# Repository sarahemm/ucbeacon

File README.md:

# ucbeacon
Unicamp Campsite Beacon

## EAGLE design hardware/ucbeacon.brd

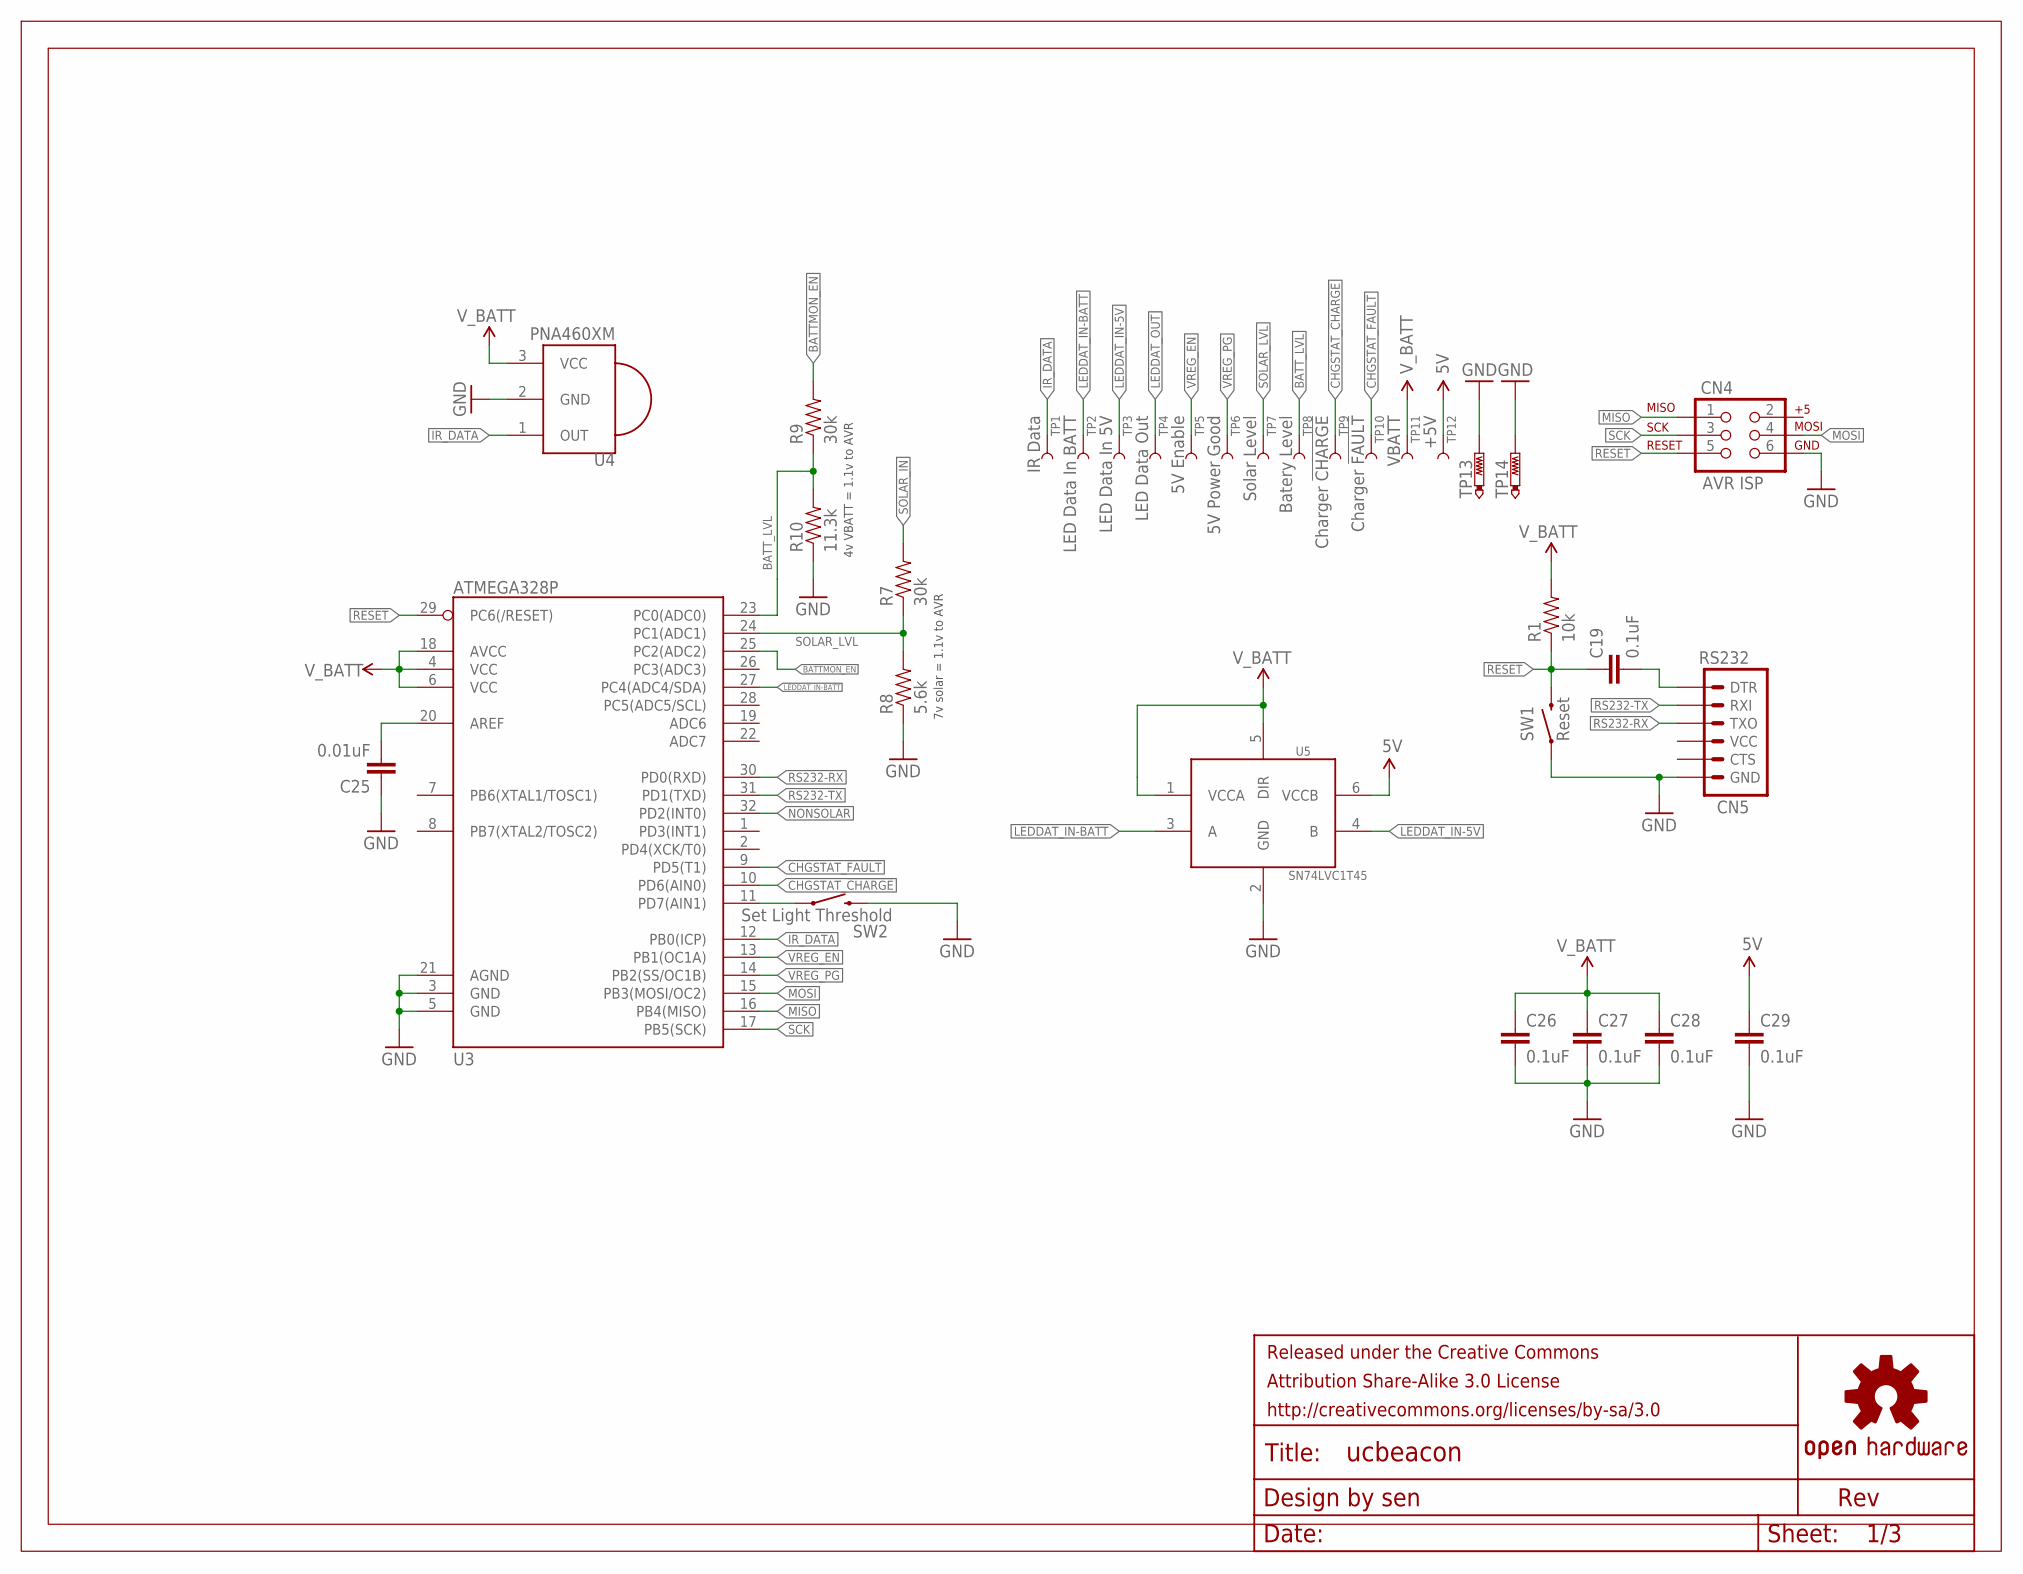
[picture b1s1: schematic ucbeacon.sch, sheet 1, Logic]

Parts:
C19, C26, C27, C28, C29: 0.1uF; 0603-CAP
C25: 0.01uF; 0603-CAP
CN4: AVR ISP; 2X3_LOCK
CN5: RS232; 1X06_LOCK
FRAME2: FRAME-LETTER-GRID-OSHW-SENOSHW-LOGO-L; OSHW-LOGO-L
R1: 10k; 0603-RES
R7, R9: 30k; 0603-RES
R8: 5.6k; 0603-RES
R10: 11.3k; 0603-RES
SW1: Reset; TACTILE_SWITCH_TALL
SW2: Set Light Threshold; TACTILE_SWITCH_TALL
TP1: IR Data; TP_15TH-MASKBOT
TP2: LED Data In BATT; TP_15TH-MASKBOT
TP3: LED Data In 5V; TP_15TH-MASKBOT
TP4: LED Data Out; TP_15TH-MASKBOT
TP5: 5V Enable; TP_15TH-MASKBOT
TP6: 5V Power Good; TP_15TH-MASKBOT
TP7: Solar Level; TP_15TH-MASKBOT
TP8: Batery Level; TP_15TH-MASKBOT
TP9: Charger !CHARGE; TP_15TH-MASKBOT
TP10: Charger !FAULT; TP_15TH-MASKBOT
TP11: VBATT; TP_15TH-MASKBOT
TP12: +5V; TP_15TH
TP13, TP14: GND; P1-13
U3: ATMEGA328P; TQFP32-08
U4: PNA460XM
U5: SN74LVC1T45; SOT23-6L

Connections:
5V: C29.1, TP12.P$1, U5.6 (VCCB); also elsewhere on the board
!RESET: C19.1, CN4.5, R1.1, SW1.B2 (2), U3.29 (PC6(/RESET))
AREF: C25.2, U3.20 (AREF)
BATTMON_EN: R9.2, U3.25 (PC2(ADC2))
BATT_LVL: R9.1, R10.2, TP8.P$1, U3.23 (PC0(ADC0))
CHGSTAT_!CHARGE: TP9.P$1, U3.10 (PD6(AIN0)); also elsewhere on the board
CHGSTAT_!FAULT: TP10.P$1, U3.9 (PD5(T1)); also elsewhere on the board
DTR_RESET: C19.2, CN5.1 (DTR)
GND: C25.1, C26.2, C27.2, C28.2, C29.2, CN4.6, CN5.6 (GND), R8.1, R10.1, SW1.A2 (1), SW2.B2 (2), TP13.TP, TP14.TP, U3.3 (GND), U3.5 (GND), U3.21 (AGND), U4.2 (GND), U5.2 (GND); also elsewhere on the board
IR_DATA: TP1.P$1, U3.12 (PB0(ICP)), U4.1 (OUT)
LEDDAT_IN-5V: TP3.P$1, U5.4 (B); also elsewhere on the board
LEDDAT_IN-BATT: TP2.P$1, U3.27 (PC4(ADC4/SDA)), U5.3 (A); also elsewhere on the board
LEDDAT_OUT: TP4.P$1; also elsewhere on the board
MISO: CN4.1, U3.16 (PB4(MISO))
MOSI: CN4.4, U3.15 (PB3(MOSI/OC2))
NONSOLAR: U3.32 (PD2(INT0)); also elsewhere on the board
RS232-RX: CN5.3 (TXO), U3.30 (PD0(RXD))
RS232-TX: CN5.2 (RXI), U3.31 (PD1(TXD))
SCK: CN4.3, U3.17 (PB5(SCK))
SET_LIGHT_THRESH: SW2.A2 (1), U3.11 (PD7(AIN1))
SOLAR_IN: R7.2; also elsewhere on the board
SOLAR_LVL: R7.1, R8.2, TP7.P$1, U3.24 (PC1(ADC1))
VREG_EN: TP5.P$1, U3.13 (PB1(OC1A)); also elsewhere on the board
VREG_PG: TP6.P$1, U3.14 (PB2(SS/OC1B)); also elsewhere on the board
V_BATT: C26.1, C27.1, C28.1, R1.2, TP11.P$1, U3.4 (VCC), U3.6 (VCC), U3.18 (AVCC), U4.3 (VCC), U5.1 (VCCA), U5.5 (DIR); also elsewhere on the board

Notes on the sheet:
7v solar = 1.1v to AVR
4v VBATT = 1.1v to AVR

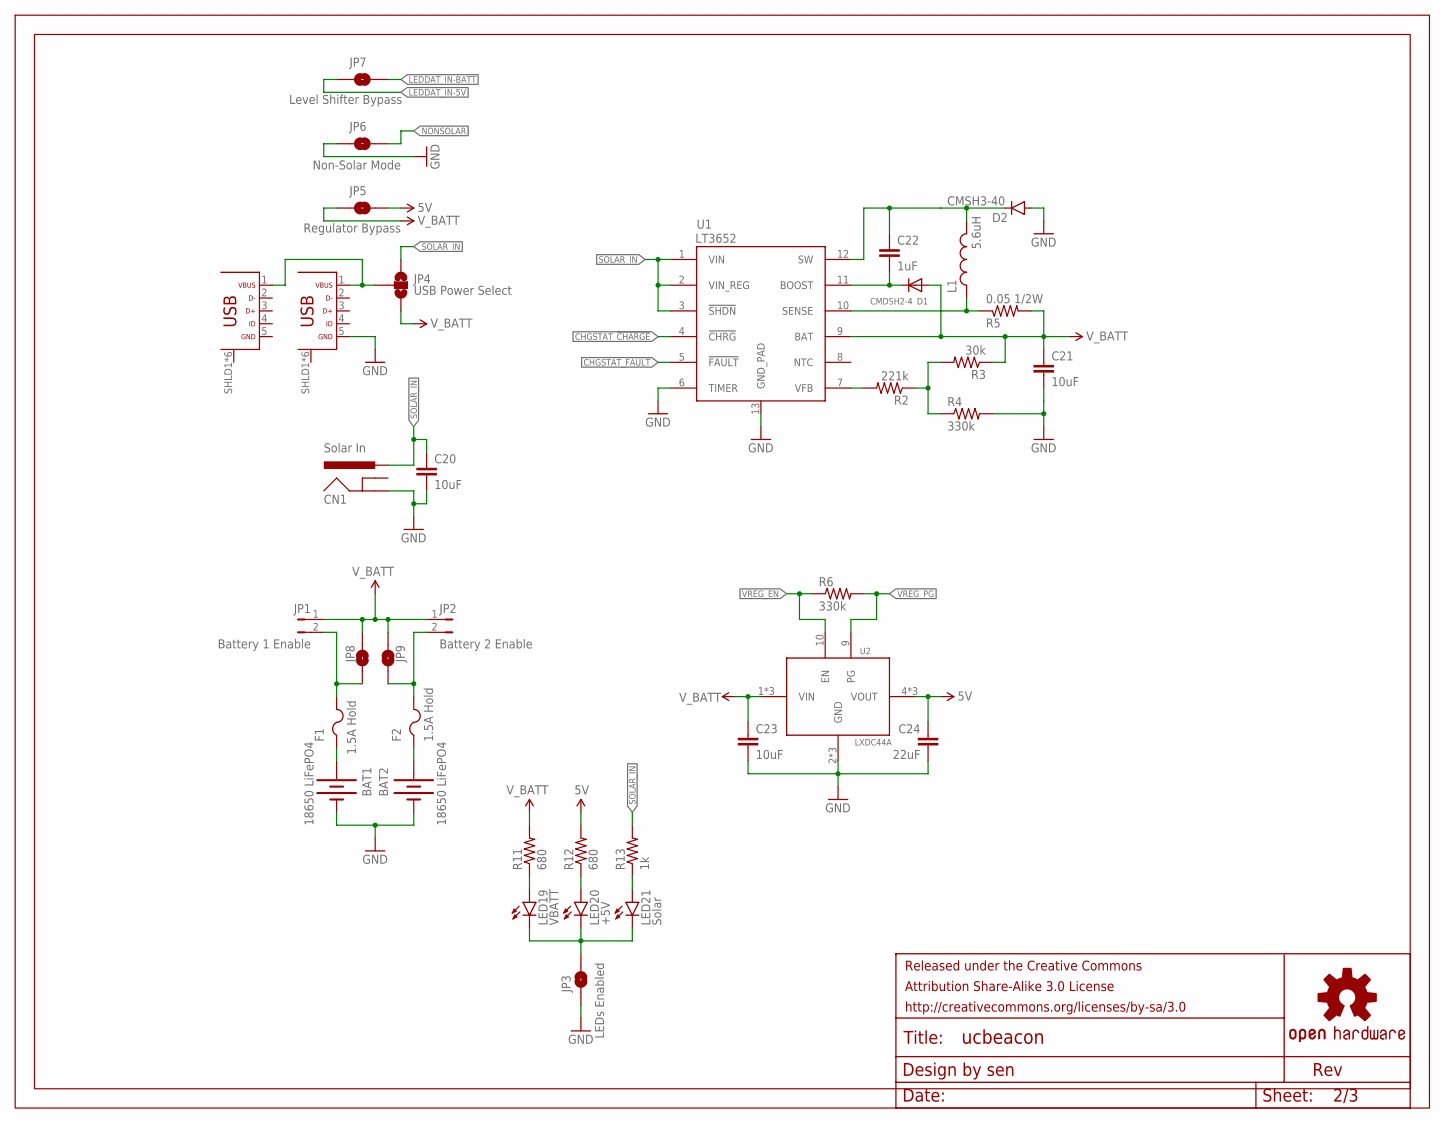
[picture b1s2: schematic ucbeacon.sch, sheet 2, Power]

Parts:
BAT1, BAT2: 18650 LiFePO4; BATTERY_18650-HOLDER
C20, C21, C23: 10uF; 0805-CAP
C22: 1uF; 0402-CAP
C24: 22uF; 0805
CN1: Solar In; POWER_JACK_PTH_LOCK
CN2: Bottom USB; FCI-10118194-MICROUSB
CN3: Top USB; FCI-10118194-MICROUSB
D1: CMDSH2-4; SOD-323F
D2: CMSH3-40; SMA-DIODE
F1, F2: 1.5A Hold; 1812
FRAME3: FRAME-LETTER-GRID-OSHW-SENOSHW-LOGO-L; OSHW-LOGO-L
JP1: Battery 1 Enable; PTH-JUMPER-2-NO_NO_SILK
JP2: Battery 2 Enable; PTH-JUMPER-2-NO_NO_SILK
JP3: LEDs Enabled; PAD-JUMPER-2-NO_YES_SILK
JP4: USB Power Select; PAD-JUMPER-3-NO_YES_SILK
JP5: Regulator Bypass; PAD-JUMPER-2-NO_YES_SILK
JP6: Non-Solar Mode; PAD-JUMPER-2-NO_YES_SILK
JP7: Level Shifter Bypass; PAD-JUMPER-2-NO_YES_SILK
JP8, JP9: Battery 1 Enable; PAD-JUMPER-2-NO_YES_SILK
L1: 5.6uH; PULSE-P1167
LED19: VBATT; LED-1206
LED20: +5V; LED-1206
LED21: Solar; LED-1206
R2: 221k; 0603-RES
R3: 30k; 0603-RES
R4, R6: 330k; 0603-RES
R5: 0.05 1/2W; 1206
R11, R12: 680; 0603-RES
R13: 1k; 0603-RES
U1: LT3652; MSOP-12_GND
U2: LXDC44A

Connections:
5V: C24.1, JP5.2, R12.2, U2.4 (VOUT), U2.5 (VOUT), U2.6 (VOUT); also elsewhere on the board
5V_LED: LED20.A, R12.1
BAT1_F: BAT1.PWR@1 (+), F1.1
BAT1_PREJMP: F1.2, JP1.2, JP8.2
BAT2_F: BAT2.PWR@1 (+), F2.1
BAT2_PREJMP: F2.2, JP2.2, JP9.2
CHGSTAT_!CHARGE: U1.4 (!CHRG); also elsewhere on the board
CHGSTAT_!FAULT: U1.5 (!FAULT); also elsewhere on the board
CHG_BOOST: C22.2, D1.C, U1.11 (BOOST)
CHG_SENSE: L1.2, R5.1, U1.10 (SENSE)
CHG_SW: C22.1, D2.C, L1.1, U1.12 (SW)
CHG_VFB: R2.2, U1.7 (VFB)
CHG_VFB_CTR: R2.1, R3.2, R4.1
GND: BAT1.GND@1 (-), BAT2.GND@1 (-), C20.2, C21.2, C23.2, C24.2, CN1.GND, CN2.5 (GND), CN3.5 (GND), D2.A, JP3.1, JP6.1, R4.2, U1.6 (TIMER), U1.13 (GND_PAD), U2.2 (GND), U2.3 (GND), U2.8 (GND); also elsewhere on the board
LEDDAT_IN-5V: JP7.1; also elsewhere on the board
LEDDAT_IN-BATT: JP7.2; also elsewhere on the board
LED_GND: JP3.2, LED19.C, LED20.C, LED21.C
NONSOLAR: JP6.2; also elsewhere on the board
SOLAR_IN: C20.1, CN1.PWR, JP4.1, R13.2, U1.1 (VIN), U1.2 (VIN_REG), U1.3 (!SHDN); also elsewhere on the board
SOLAR_LED: LED21.A, R13.1
USB_VBUS: CN2.1 (VBUS), CN3.1 (VBUS), JP4.2
VBATT_LED: LED19.A, R11.1
VREG_EN: R6.1, U2.10 (EN); also elsewhere on the board
VREG_PG: R6.2, U2.9 (PG); also elsewhere on the board
V_BATT: C21.1, C23.1, D1.A, JP1.1, JP2.1, JP4.3, JP5.1, JP8.1, JP9.1, R3.1, R5.2, R11.2, U1.9 (BAT), U2.1 (VIN), U2.11 (VIN), U2.12 (VIN); also elsewhere on the board

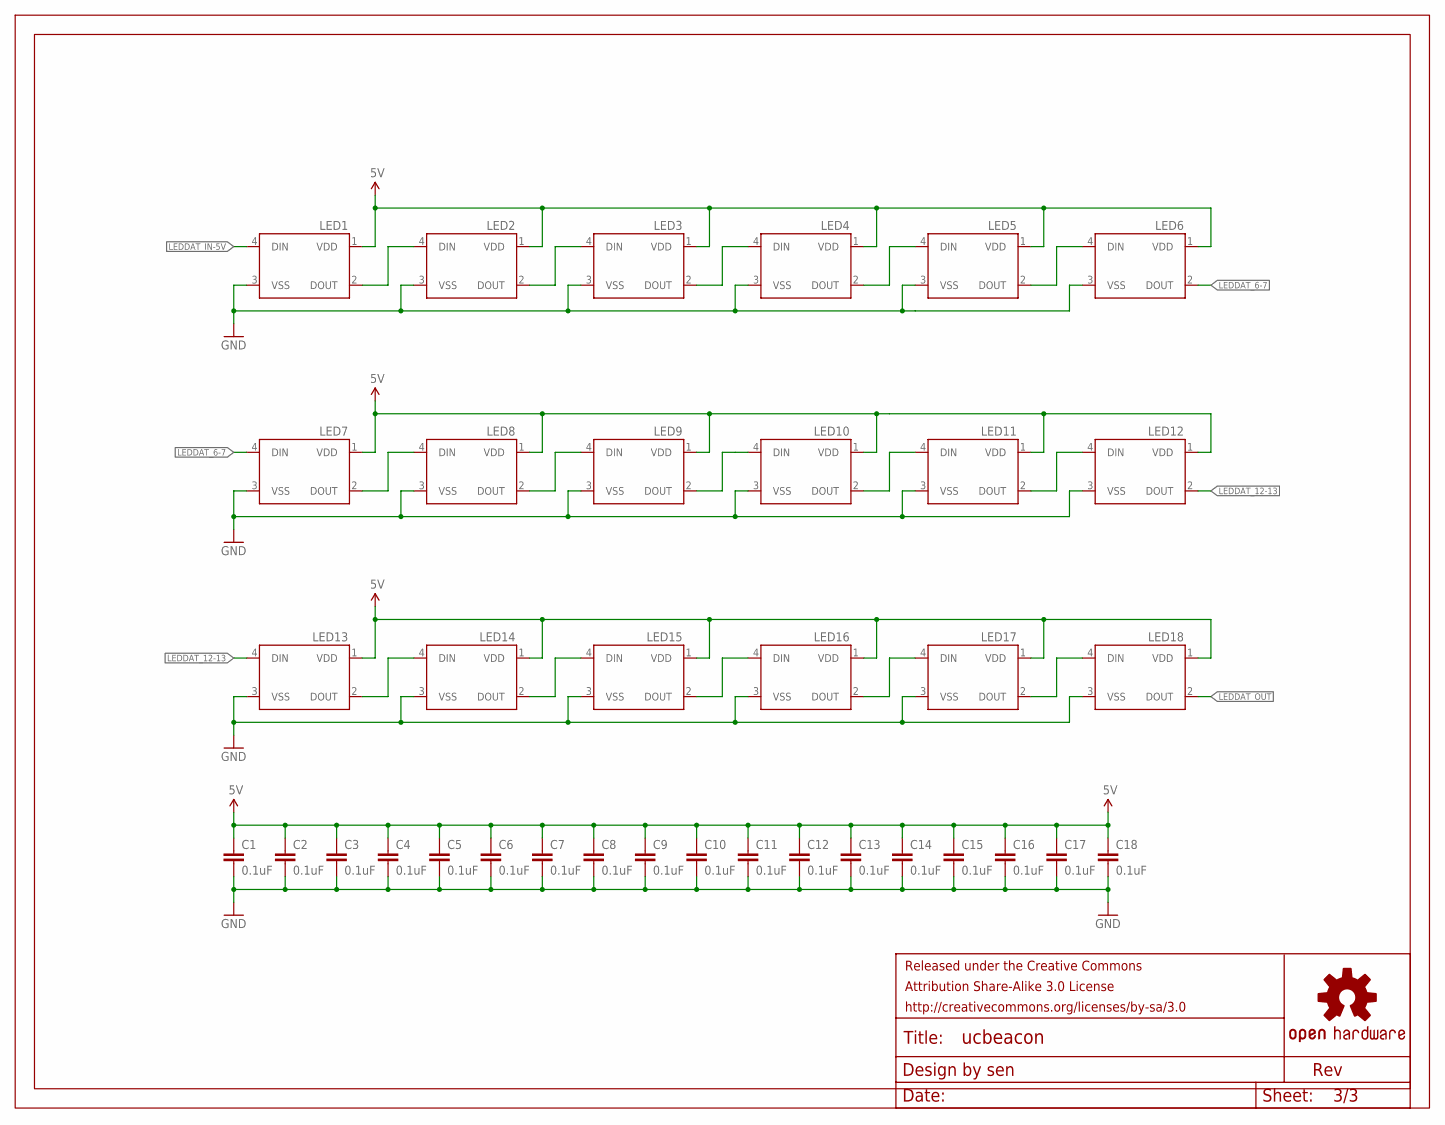
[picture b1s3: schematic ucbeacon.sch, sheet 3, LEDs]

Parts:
C1, C2, C3, C4, C5, C6, C7, C8, C9, C10, C11, C12, C13, C14, C15, C16, C17, C18: 0.1uF; 0603-CAP
FRAME1: FRAME-LETTER-GRID-OSHW-SENOSHW-LOGO-L; OSHW-LOGO-L
LED1, LED2, LED3, LED4, LED5, LED6, LED7, LED8, LED9, LED10, LED11, LED12, LED13, LED14, LED15, LED16, LED17, LED18: WS2812B

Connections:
5V: C1.1, C2.1, C3.1, C4.1, C5.1, C6.1, C7.1, C8.1, C9.1, C10.1, C11.1, C12.1, C13.1, C14.1, C15.1, C16.1, C17.1, C18.1, LED1.1 (VDD), LED2.1 (VDD), LED3.1 (VDD), LED4.1 (VDD), LED5.1 (VDD), LED6.1 (VDD), LED7.1 (VDD), LED8.1 (VDD), LED9.1 (VDD), LED10.1 (VDD), LED11.1 (VDD), LED12.1 (VDD), LED13.1 (VDD), LED14.1 (VDD), LED15.1 (VDD), LED16.1 (VDD), LED17.1 (VDD), LED18.1 (VDD); also elsewhere on the board
GND: C1.2, C2.2, C3.2, C4.2, C5.2, C6.2, C7.2, C8.2, C9.2, C10.2, C11.2, C12.2, C13.2, C14.2, C15.2, C16.2, C17.2, C18.2, LED1.3 (VSS), LED2.3 (VSS), LED3.3 (VSS), LED4.3 (VSS), LED5.3 (VSS), LED6.3 (VSS), LED7.3 (VSS), LED8.3 (VSS), LED9.3 (VSS), LED10.3 (VSS), LED11.3 (VSS), LED12.3 (VSS), LED13.3 (VSS), LED14.3 (VSS), LED15.3 (VSS), LED16.3 (VSS), LED17.3 (VSS), LED18.3 (VSS); also elsewhere on the board
LEDDAT_1-2: LED1.2 (DOUT), LED2.4 (DIN)
LEDDAT_2-3: LED2.2 (DOUT), LED3.4 (DIN)
LEDDAT_3-4: LED3.2 (DOUT), LED4.4 (DIN)
LEDDAT_4-5: LED4.2 (DOUT), LED5.4 (DIN)
LEDDAT_5-6: LED5.2 (DOUT), LED6.4 (DIN)
LEDDAT_6-7: LED6.2 (DOUT), LED7.4 (DIN)
LEDDAT_7-8: LED7.2 (DOUT), LED8.4 (DIN)
LEDDAT_8-9: LED8.2 (DOUT), LED9.4 (DIN)
LEDDAT_9-10: LED9.2 (DOUT), LED10.4 (DIN)
LEDDAT_10-11: LED10.2 (DOUT), LED11.4 (DIN)
LEDDAT_11-12: LED11.2 (DOUT), LED12.4 (DIN)
LEDDAT_12-13: LED12.2 (DOUT), LED13.4 (DIN)
LEDDAT_13-14: LED13.2 (DOUT), LED14.4 (DIN)
LEDDAT_14-15: LED14.2 (DOUT), LED15.4 (DIN)
LEDDAT_15-16: LED15.2 (DOUT), LED16.4 (DIN)
LEDDAT_16-17: LED16.2 (DOUT), LED17.4 (DIN)
LEDDAT_17-18: LED17.2 (DOUT), LED18.4 (DIN)
LEDDAT_IN-5V: LED1.4 (DIN); also elsewhere on the board
LEDDAT_OUT: LED18.2 (DOUT); also elsewhere on the board

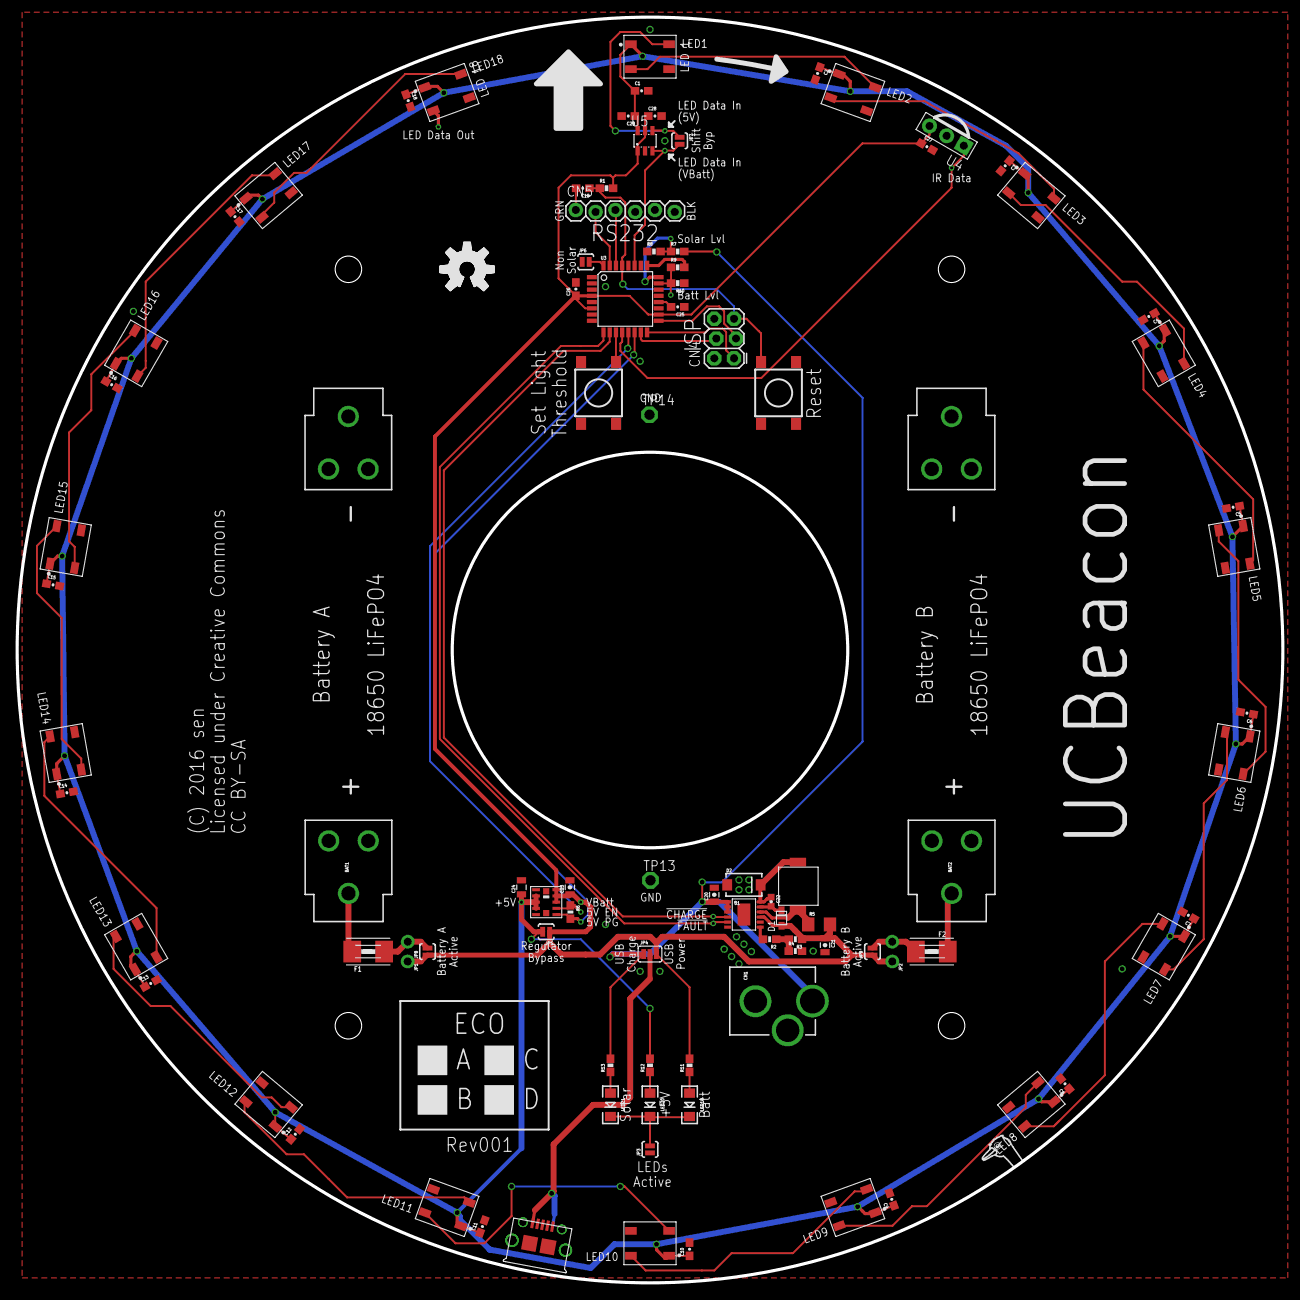
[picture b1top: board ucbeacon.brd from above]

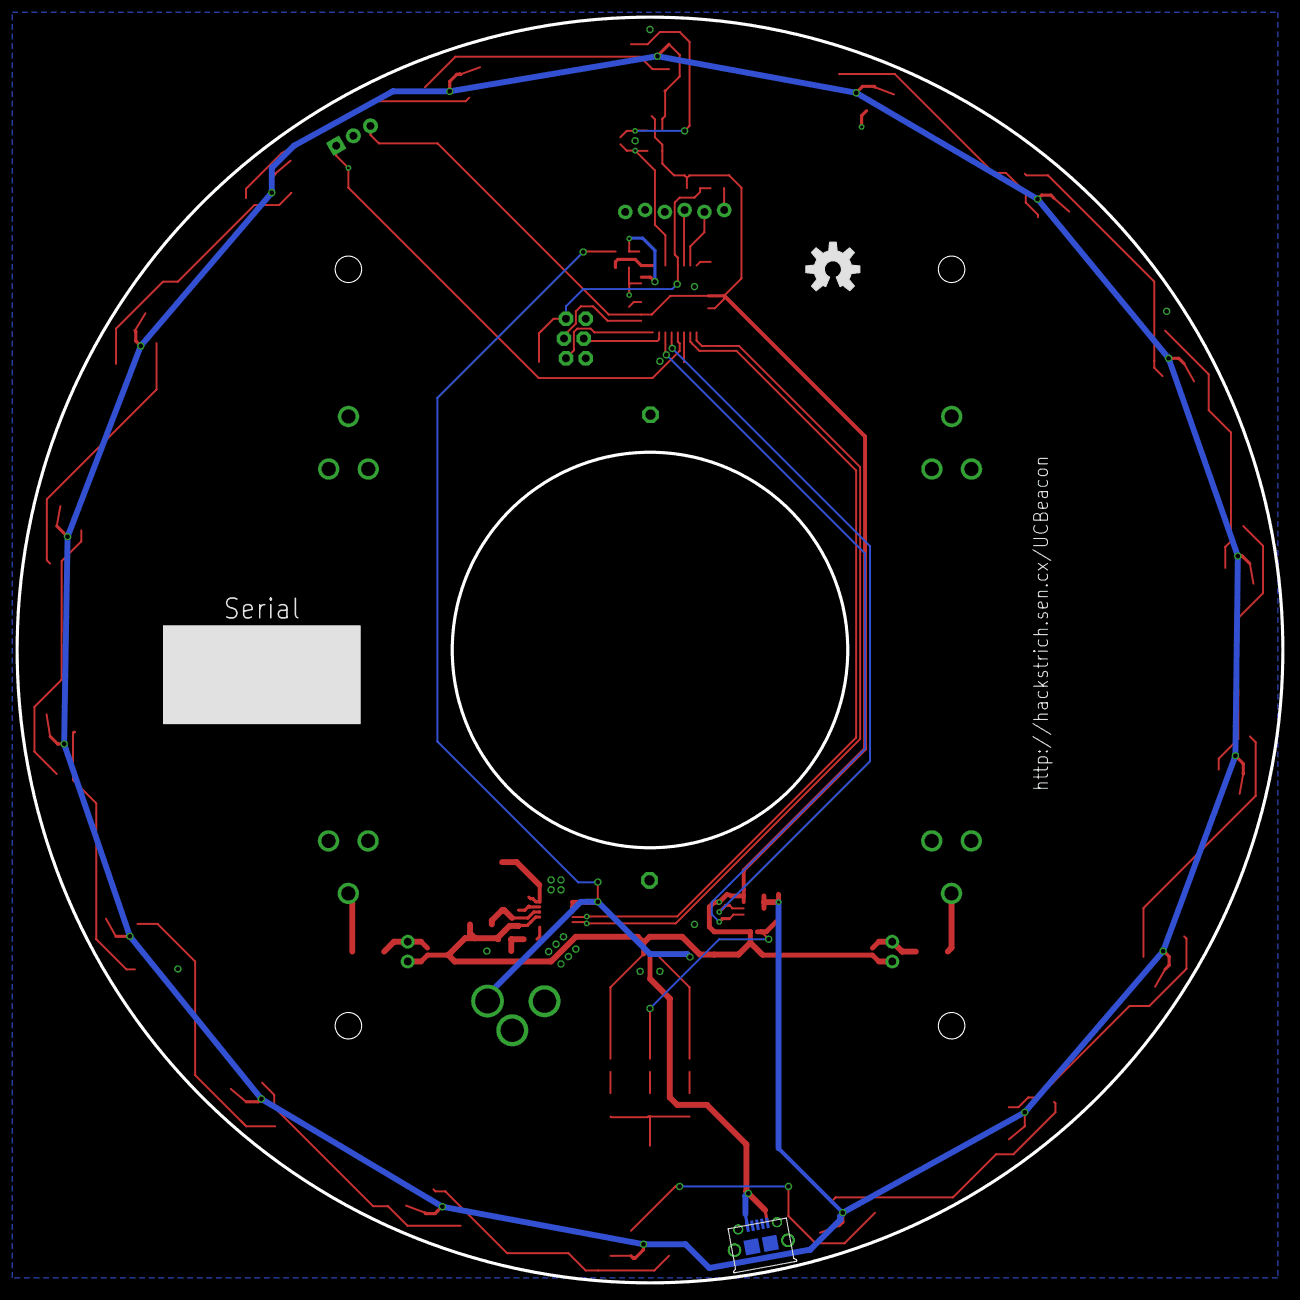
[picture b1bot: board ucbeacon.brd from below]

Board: 2 copper layers, 162.6 x 162.6 mm, 109 parts (2 on the bottom side), 56 nets.

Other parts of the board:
U$1: STRICH-LOGO

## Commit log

2016-06-21 Adding current version of the 3D model of UCBeacon.
2016-06-21 Adding README for the 3D model.
2016-08-04 Initial work on schematic for UCBeacon. Logic, LEDs, and charging mostly done.
2016-08-06 Almost done hardware design, still need to complete solar switch.
2016-08-07 Completed schematic, still need to run through checklist.
2016-08-10 Completed design and checklisted it.
2016-08-10 Started routing board.
2016-08-18 Added option to run from USB power rather than solar/battery.
2016-08-22 Routing complete, pending board checklisting.
2016-08-27 Added silkscreen and started running through checklist.
2016-09-04 Completed PCB and checklist.
2016-09-04 Board test points tweaked and CAM output, checklist complete.

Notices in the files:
hardware/ucbeacon.brd:
(C) 2016 sen
Licensed under Creative Commons
CC BY-SA
parts and their libraries:
SparkFun-LED: Licensing: Creative Commons ShareAlike 4.0 International - https://creativecommons.org/licenses/by-sa/4.0
logos-sen: Released under the Creative Commons Attribution Share-Alike 3.0 License
logos-sen: http://creativecommons.org/licenses/by-sa/3.0
